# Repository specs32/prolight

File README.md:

# prolight
Gyroscope Matrix Flashlight

click the wiki button in the menu above ! ;)

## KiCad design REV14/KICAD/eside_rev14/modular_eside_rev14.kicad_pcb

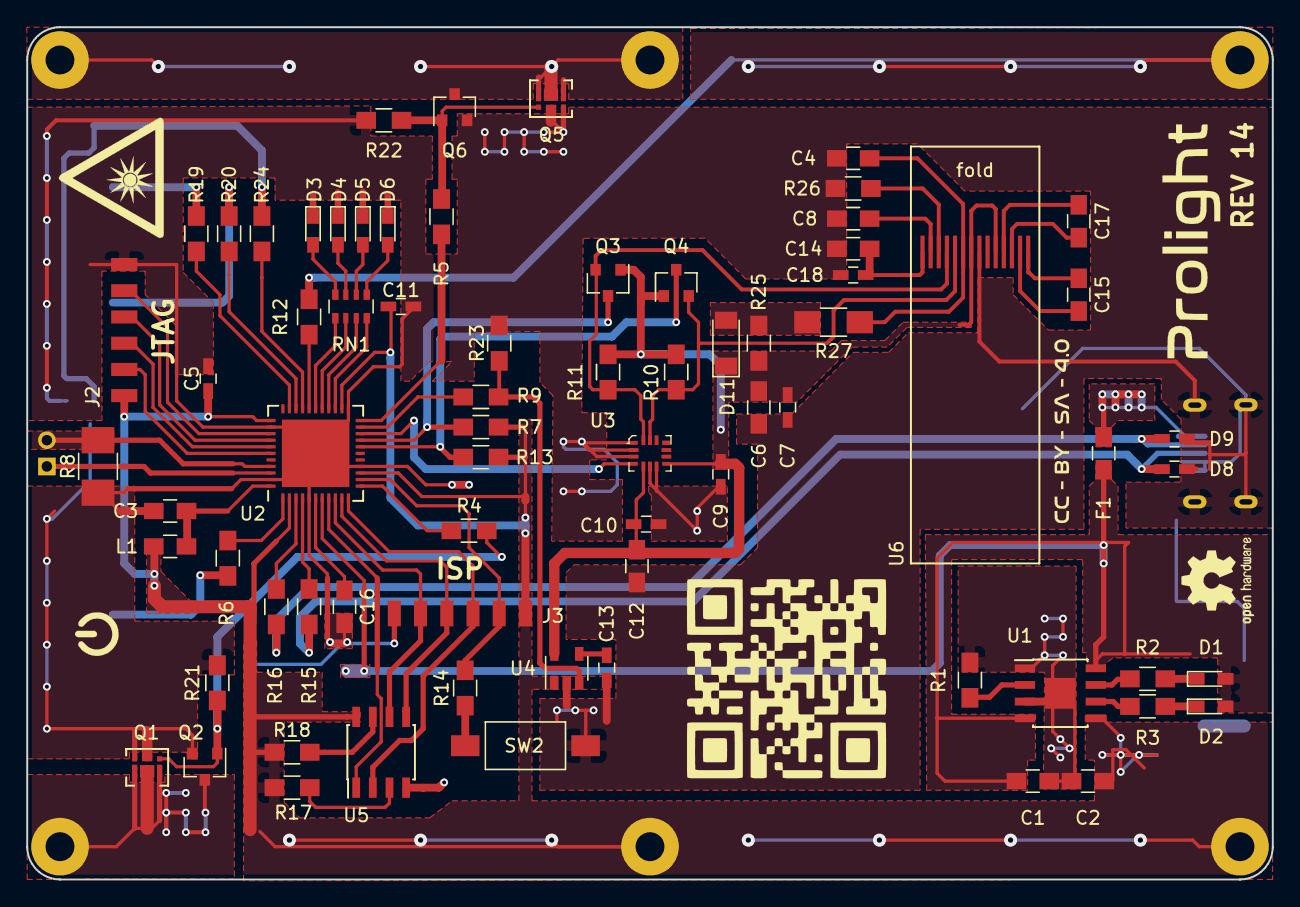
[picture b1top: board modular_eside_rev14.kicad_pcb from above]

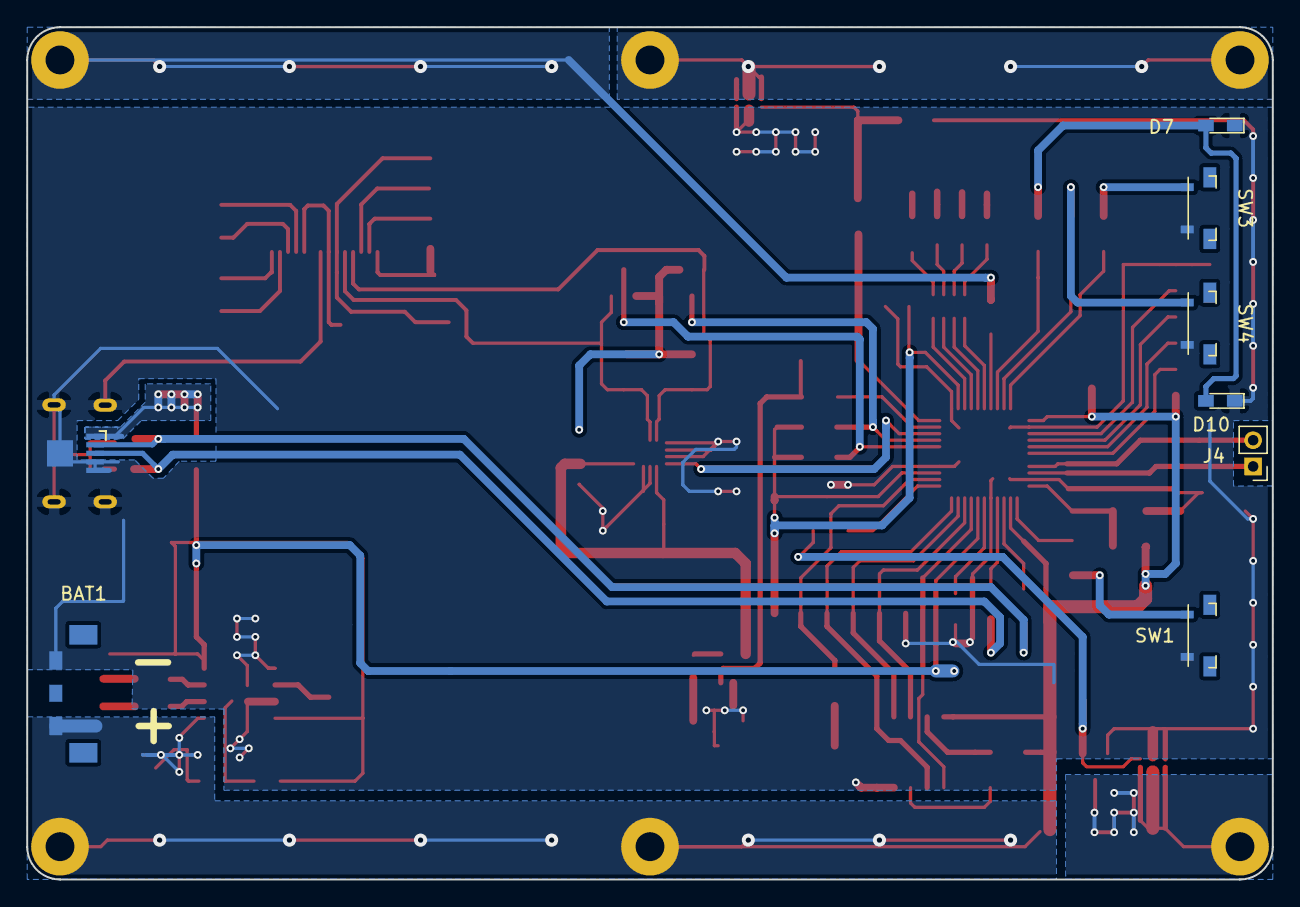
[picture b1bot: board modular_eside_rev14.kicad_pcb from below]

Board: 2 copper layers, 95.0 x 65.0 mm, 86 parts (8 on the bottom side), 71 nets.

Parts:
BAT1: LIPO_W_NTC; CONN_AVX_RT_ANGLE_3pin_2.5mm_pitch
C1, C2, C12: 10µF; C_0805_HandSoldering
C3: 100nF; C_0805_HandSoldering
C4, C6, C14: 4.7µF; C_0805_HandSoldering
C5, C7, C10, C11, C18: 100nF; C_0603_HandSoldering
C8: 2.2µF; C_0805_HandSoldering
C9: 100 nF; C_0603_HandSoldering
C13: 470pF; C_0603_HandSoldering
C15, C16, C17: 1µF; C_0805_HandSoldering
D1: RED; LED_0603_HandSoldering
D2: GREEN; LED_0603_HandSoldering
D3: STAT_RED; LED_0603_HandSoldering
D4: STAT_YELLOW; LED_0603_HandSoldering
D5: STAT_GREEN; LED_0603_HandSoldering
D6: STAT_PINK; LED_0603_HandSoldering
D7, D10: BUTTONLED_PINK; LED_0603_HandSoldering
D8, D9: D_TVS; C_0603_HandSoldering
D11: LL4148; D_MiniMELF
F1: Polyfuse_1A_hold; C_0805_HandSoldering
J1: USB_Micro_Jack; Conn_USBmicro-B_ebay-side_TH_GROUND
J2: JTAG_Conn_01x06; Conn_01x06_SMD_2mm
J3: ISP_Conn_01x06; Conn_01x06_SMD_2mm
J4: TEMP_Conn_01x02; Pin_Header_Straight_1x02_Pitch2.00mm
L1: 10µH; C_0805_HandSoldering
MK1: PWM_1; MountingHole_2.2mm_M2_Pad
MK2, MK6: MAT_PWR; MountingHole_2.2mm_M2_Pad
MK3: MAT_SIG; MountingHole_2.2mm_M2_Pad
MK4, MK5: VCC; MountingHole_2.2mm_M2_Pad
Q1, Q5: DMN1004UFDF; U-DFN2020-6-smallerpads
Q2, Q6: Q_NMOS_GSD; SOT-23
Q3, Q4: 2N7002; SOT-23
R1: 1.2KΩ; R_0805_HandSoldering
R2, R3, R4, R5, R9, R12, R24: 1KΩ; R_0805_HandSoldering
R6, R19, R20: 10KΩ; R_0805_HandSoldering
R7, R10, R11, R13: 10kΩ; R_0805_HandSoldering
R8: 15KΩ; R_1210_HandSoldering
R14: 1kΩ; R_0805_HandSoldering
R15, R16: 22Ω; R_0805_HandSoldering
R17, R18: 4.7KΩ; R_0805_HandSoldering
R21, R22, R23: 1MΩ; R_0805_HandSoldering
R25: 4.7kΩ; R_0805_HandSoldering
R26: 380kΩ; R_0805_HandSoldering
R27: 0Ω; R_1206_HandSoldering
RN1: R_Pack_1kΩ; R_Array_Convex_4x0603
SW1: SW_MODE; white_nano_smd_switch
SW2: SW_MODE; SW_SPST_FSMSM
SW3: SW_UP; white_nano_smd_switch
SW4: SW_DOWN; white_nano_smd_switch
U1: TP4056; SOIC-8-1EP_3.9x4.9mm_Pitch1.27mm
U2: ATMEGA32U4-RC-MU; QFN-44-1EP_7x7mm_Pitch0.5mm
U3: LSM6DS3TR; LGA-14L_2.5x3mm__LSM6DS3
U4: MIC5205-3.3; SOT-23-5
U5: AT25_EEPROM; SOIC-8_3.9x4.9mm_Pitch1.27mm
U6: OLED_0.86_14PIN; OLED_0.86_14pin_i2c

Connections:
+3V3: C6.1, C7.1, C9.1, C10.1, C12.1, D11.1, Q3.1, Q4.1, R10.1, R11.1, R25.2, U3.5, U3.8, U4.5, U6.5, U6.8
/MAT_SIG: MK3.1, R12.2
ADC0: J4.2, R8.2, U2.41
AREF: J4.1, U2.42
AVCC: C3.1, L1.2, U2.44
CHRG: R2.2, U1.7
CS: U2.8, U5.1
D+: D8.1, J1.3, R15.2
D-: D9.1, J1.2, R16.2
GND: BAT1.1, C1.2, C2.2, C3.2, C4.1, C5.2, C6.2, C7.2, C8.1, C9.2, C10.2, C11.2, C12.2, C13.2, C14.2, C16.2, C18.2, D3.1, D4.1, D5.1, D6.1, D7.1, D8.2, D9.2, D10.1, J1.4, J1.5, J2.6, J3.6, Q1.2, Q2.2, Q5.2, Q6.2, R1.1, R8.1, R21.2, R22.2, R23.2, R26.2, SW1.2, SW2.2, SW3.2, SW4.2, U1.1, U1.3, U1.9, U2.5, U2.15, U2.23, U2.35, U2.43, U2.45, U3.1, U3.2, U3.3, U3.6, U3.7, U4.2, U5.4, U6.7
INT2_ACC-INT1: U2.20, U3.4
INT6_SW1: R6.2, U2.1
MAT_PWR: MK2.1, MK6.1, Q5.1, Q6.3
MISO: J3.3, U2.11, U5.2
MOSI: J3.4, U2.10, U5.5
unnamed: C4.2, R27.2, U6.9
unnamed: C8.2, U6.13
unnamed: C13.1, U4.4
unnamed: C14.1, C18.1, U6.14
unnamed: C15.1, U6.1
unnamed: C15.2, U6.2
unnamed: C16.1, U2.6
unnamed: C17.1, U6.3
unnamed: C17.2, U6.4
unnamed: D1.1, R2.1
unnamed: D2.1, R3.1
unnamed: D3.2, RN1.8
unnamed: D4.2, RN1.7
unnamed: D5.2, RN1.6
unnamed: D6.2, RN1.5
unnamed: D7.2, D10.2, R24.2
unnamed: D11.2, R25.1, R27.1
unnamed: F1.2, J1.1
unnamed: Q1.3, Q2.1, R4.2, R21.1
unnamed: Q5.3, Q6.1, R5.2, R22.1
unnamed: R6.1, SW1.1
unnamed: R14.1, SW2.1
unnamed: R15.1, U2.4
unnamed: R16.1, U2.3
unnamed: R17.2, U5.3
unnamed: R18.2, U5.7
unnamed: R19.1, SW3.1
unnamed: R20.1, SW4.1
unnamed: R9.2, R23.1, U4.3
unnamed: R26.1, U6.12
OC1A: R12.1, U2.29
OC1C: R4.1, U2.12
PB4_LED4: RN1.1, U2.28
PB6_BUTTONLED: R24.1, U2.30
PC6_SW3: R20.2, U2.31
PC7_SW3: R19.2, U2.32
PD3_3V3_SW: R9.1, U2.21
PD4_LED1: RN1.4, U2.25
PD5_MATRIX_SW: R5.1, U2.22
PD6_LED2: RN1.3, U2.26
PD7_LED3: RN1.2, U2.27
PRG: R1.2, U1.2
PWM_1: MK1.1, Q1.1, Q2.3
RESET: J3.2, R14.2, U2.13
SCK: J3.5, U2.9, U5.6
SCL: Q4.3, R13.2, U2.18
SCL_3V3: Q4.2, R10.2, U3.13, U6.10
SDA: Q3.3, R7.2, U2.19
SDA_3V3: Q3.2, R11.2, U3.14, U6.11
STDBY: R3.2, U1.6
TCK: J2.2, U2.39
TDI: J2.5, U2.36
TDO: J2.4, U2.37
TMS: J2.3, U2.38
VBUS: C1.1, D1.2, D2.2, F1.1, U1.4, U1.8, U2.7
VCC: BAT1.3, C2.1, C5.1, C11.1, J2.1, J3.1, L1.1, MK4.1, MK5.1, R7.1, R13.1, R17.1, R18.1, U1.5, U2.2, U2.14, U2.24, U2.34, U4.1, U5.8

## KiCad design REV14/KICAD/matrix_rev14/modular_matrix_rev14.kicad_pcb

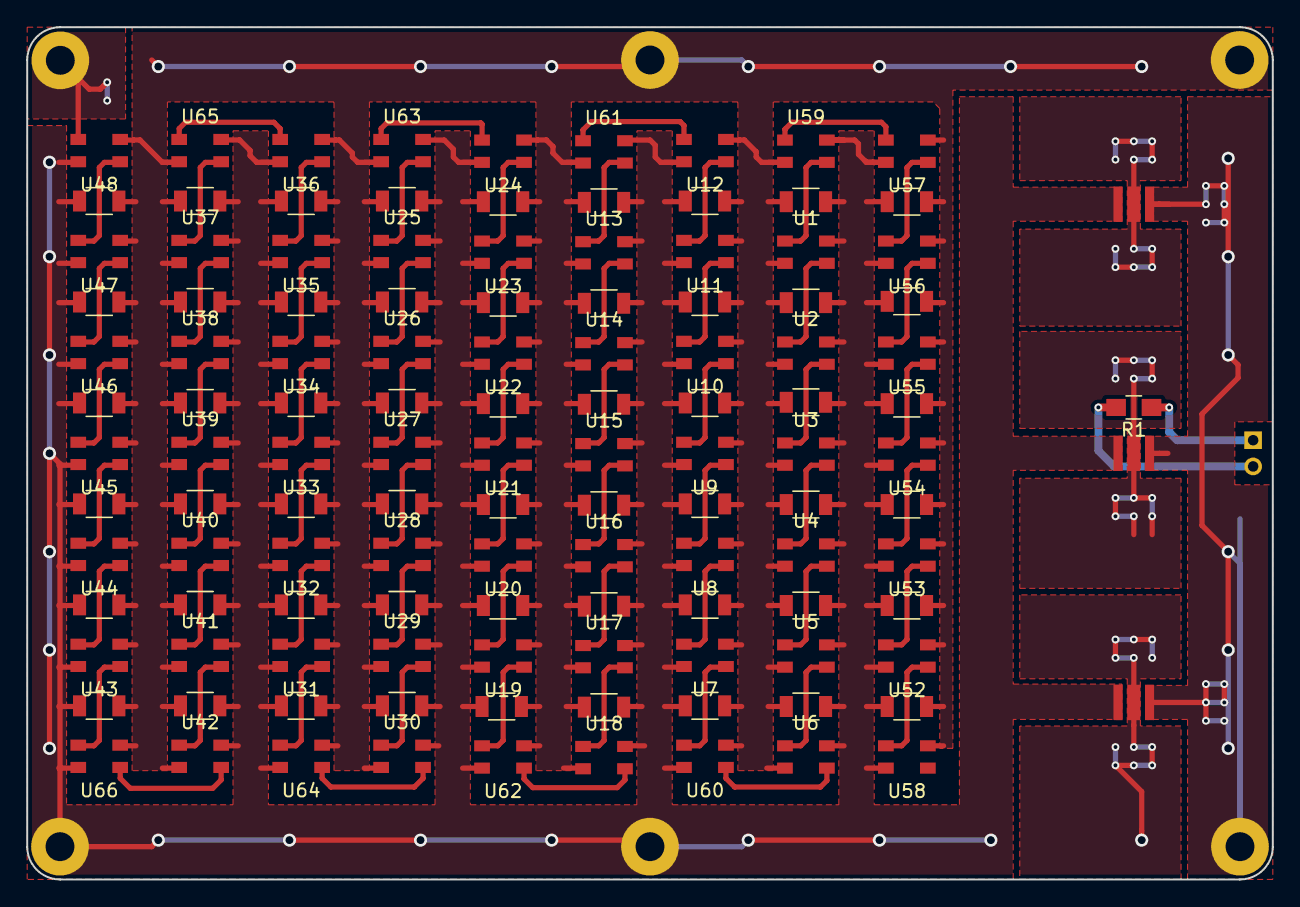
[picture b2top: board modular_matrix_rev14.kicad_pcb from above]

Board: 2 copper layers, 95.0 x 65.0 mm, 128 parts (1 on the bottom side), 68 nets.

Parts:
C1, C2, C3, C4, C5, C7, C8, C9, C10, C11, C13, C14, C15, C16, C17, C19, C20, C21, C22, C23, C24, C25, C26, C27, C28, C29, C30, C31, C32, C33, C34, C35, C36, C37, C38, C39, C40, C41, C42, C43, C44, C45, C46, C47, C48, C49, C50, C51, C52, C53, C54, C55, C56, C57: 100nF; C_1206
D1, D2, D3: LED_oslon_ssl80; LED_osram_oslon_ssl_powerled
J1: Conn_01x02_Male; Pin_Header_Straight_1x02_Pitch2.00mm
MK1: VCC; MountingHole_2.2mm_M2_Pad
MK2: OC1A; MountingHole_2.2mm_M2_Pad
MK3, MK5: GND; MountingHole_2.2mm_M2_Pad
MK4: PWM_1; MountingHole_2.2mm_M2_Pad
MK6: VCC_OPT; MountingHole_2.2mm_M2_Pad
R1: 10KΩ NTC; R_0805_HandSoldering
U1, U2, U3, U4, U5, U6, U7, U8, U9, U10, U11, U12, U13, U14, U15, U16, U17, U18, U19, U20, U21, U22, U23, U24, U25, U26, U27, U28, U29, U30, U31, U32, U33, U34, U35, U36, U37, U38, U39, U40, U41, U42, U43, U44, U45, U46, U47, U48, U52, U53, U54, U55, U56, U57, U58, U59, U60, U61, U62, U63, U64, U65, U66: RGB_ws2812_3535; SK6812_3535

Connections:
GND: C1.2, C2.2, C3.2, C4.2, C5.2, C7.2, C8.2, C9.2, C10.2, C11.2, C13.2, C14.2, C15.2, C16.2, C17.2, C19.2, C20.2, C21.2, C22.2, C23.2, C24.2, C25.2, C26.2, C27.2, C28.2, C29.2, C30.2, C31.2, C32.2, C33.2, C34.2, C35.2, C36.2, C37.2, C38.2, C39.2, C40.2, C41.2, C42.2, C43.2, C44.2, C45.2, C46.2, C47.2, C48.2, C49.2, C50.2, C51.2, C52.2, C53.2, C54.2, C55.2, C56.2, C57.2, MK3.1, MK5.1, U1.2, U2.2, U3.2, U4.2, U5.2, U6.2, U7.2, U8.2, U9.2, U10.2, U11.2, U12.2, U13.2, U14.2, U15.2, U16.2, U17.2, U18.2, U19.2, U20.2, U21.2, U22.2, U23.2, U24.2, U25.2, U26.2, U27.2, U28.2, U29.2, U30.2, U31.2, U32.2, U33.2, U34.2, U35.2, U36.2, U37.2, U38.2, U39.2, U40.2, U41.2, U42.2, U43.2, U44.2, U45.2, U46.2, U47.2, U48.2, U52.2, U53.2, U54.2, U55.2, U56.2, U57.2, U58.2, U59.2, U60.2, U61.2, U62.2, U63.2, U64.2, U65.2, U66.2
unnamed: J1.1, R1.1
unnamed: J1.2, R1.2
unnamed: U1.1, U59.3
unnamed: U1.3, U2.1
unnamed: U2.3, U3.1
unnamed: U3.3, U4.1
unnamed: U4.3, U5.1
unnamed: U5.3, U6.1
unnamed: U6.3, U60.1
unnamed: U7.3, U8.1
unnamed: U8.3, U9.1
unnamed: U9.3, U10.1
unnamed: U10.3, U11.1
unnamed: U11.3, U12.1
unnamed: U12.3, U61.1
unnamed: U13.1, U61.3
unnamed: U13.3, U14.1
unnamed: U14.3, U15.1
unnamed: U15.3, U16.1
unnamed: U16.3, U17.1
unnamed: U17.3, U18.1
unnamed: U18.3, U62.1
unnamed: U19.1, U62.3
unnamed: U19.3, U20.1
unnamed: U20.3, U21.1
unnamed: U21.3, U22.1
unnamed: U22.3, U23.1
unnamed: U23.3, U24.1
unnamed: U24.3, U63.1
unnamed: U25.1, U63.3
unnamed: U25.3, U26.1
unnamed: U26.3, U27.1
unnamed: U27.3, U28.1
unnamed: U28.3, U29.1
unnamed: U29.3, U30.1
unnamed: U30.3, U64.1
unnamed: U31.1, U64.3
unnamed: U31.3, U32.1
unnamed: U32.3, U33.1
unnamed: U33.3, U34.1
unnamed: U34.3, U35.1
unnamed: U35.3, U36.1
unnamed: U36.3, U65.1
unnamed: U37.1, U65.3
unnamed: U37.3, U38.1
unnamed: U38.3, U39.1
unnamed: U39.3, U40.1
unnamed: U40.3, U41.1
unnamed: U41.3, U42.1
unnamed: U42.3, U66.1
unnamed: U43.1, U66.3
unnamed: U43.3, U44.1
unnamed: U44.3, U45.1
unnamed: U45.3, U46.1
unnamed: U46.3, U47.1
unnamed: U47.3, U48.1
unnamed: U52.1, U58.3
unnamed: U52.3, U53.1
unnamed: U53.3, U54.1
unnamed: U54.3, U55.1
unnamed: U55.3, U56.1
unnamed: U56.3, U57.1
unnamed: U57.3, U59.1
unnamed: U7.1, U60.3
OC1A: MK2.1, U48.3
PWM_1: D1.1, D2.1, D3.1, MK4.1
VCC: C1.1, C2.1, C3.1, C4.1, C5.1, C7.1, C8.1, C9.1, C10.1, C11.1, C13.1, C14.1, C15.1, C16.1, C17.1, C19.1, C20.1, C21.1, C22.1, C23.1, C24.1, C25.1, C26.1, C27.1, C28.1, C29.1, C30.1, C31.1, C32.1, C33.1, C34.1, C35.1, C36.1, C37.1, C38.1, C39.1, C40.1, C41.1, C42.1, C43.1, C44.1, C45.1, C46.1, C47.1, C48.1, C49.1, C50.1, C51.1, C52.1, C53.1, C54.1, C55.1, C56.1, C57.1, D1.2, D2.2, D3.2, MK1.1, MK6.1, U1.4, U2.4, U3.4, U4.4, U5.4, U6.4, U7.4, U8.4, U9.4, U10.4, U11.4, U12.4, U13.4, U14.4, U15.4, U16.4, U17.4, U18.4, U19.4, U20.4, U21.4, U22.4, U23.4, U24.4, U25.4, U26.4, U27.4, U28.4, U29.4, U30.4, U31.4, U32.4, U33.4, U34.4, U35.4, U36.4, U37.4, U38.4, U39.4, U40.4, U41.4, U42.4, U43.4, U44.4, U45.4, U46.4, U47.4, U48.4, U52.4, U53.4, U54.4, U55.4, U56.4, U57.4, U58.4, U59.4, U60.4, U61.4, U62.4, U63.4, U64.4, U65.4, U66.4

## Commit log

2018-04-05 Set theme jekyll-theme-minimal
2018-04-05 addsome
2018-04-05 Rename rev11.md to readme.md
2018-04-05 addmore
2018-04-27 initial release
    WIP !
    bare minimum to run the light, check temps, and voltages and power down
2018-05-01 added some gyro stuff
    added reinit twi after sleep
    added levels (matrix gyro)
    few other minor corretions
2018-05-02 pushed REV 14
2018-05-02 added changes for the prolight
2018-05-12 all fine so far...
    external SPI flash still needs implementation
